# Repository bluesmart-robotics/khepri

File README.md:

# KHÉPRI — Blue Smart Robotics

- [`IHM/`](IHM/) : écrans pilote — rond 1,75" (régime moteur) et rectangulaire 1,64" (énergie),
  sur cartes Waveshare ESP32-S3-Touch-AMOLED — documentation et code, mises à jour OTA depuis ce dépôt.
- [`hardware/BSR flight power module/`](hardware/BSR%20flight%20power%20module/) : instrument de vol
  de 80 mm — commande moteur BSR Drive v3.7 (sous-module), carte de contrôle CAN et interface pilote.
  Contient un sous-module : cloner avec `--recurse-submodules`.
  - [`ecran_rond_1.75/`](hardware/BSR%20flight%20power%20module/ecran_rond_1.75/) : carte écran rond
    1,75" propre à KHEPRI (KiCad 9), dérivée de la Waveshare sans PMU/batterie, micros ni IMU —
    schéma complet, PCB Ø46 mm à router.

L'ancien code de démonstration de l'écran AMOLED 1,64" (bsr_screen) reste consultable dans
l'historique Git (commit 8a9e916).

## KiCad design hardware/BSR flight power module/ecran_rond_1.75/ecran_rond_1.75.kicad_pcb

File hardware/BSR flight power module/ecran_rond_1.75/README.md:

# Écran rond 1,75" KHEPRI — carte dérivée de la Waveshare ESP32-S3-Touch-AMOLED-1.75-G

Reproduction en KiCad 9 de la carte Waveshare **ESP32-S3-Touch-AMOLED-1.75(-G)** (écran AMOLED rond
466×466 sur ESP32-S3R8), adaptée à l'instrument de bord KHEPRI :

- **supprimé** : gestion de batterie (AXP2101, connecteur batterie, bouton PWR), micros et leur ADC
  (ES7210, 2 micros MEMS, circuit d'annulation d'écho), centrale inertielle (QMI8658) ;
- **ajouté / modifié** : entrée 5 V sur connecteur JST PH 4 points (+5 V, GND, TX, RX) partagé avec
  l'UART vers la carte façade, buck AP63203 3,3 V 2 A (même famille que l'AP63205 de la carte de
  contrôle), pile CR1220 (support CMS, côté écran) pour la RTC et le GPS externe ;
- **GPS déporté** : le module LC76G et son antenne sont retirés de la carte (place nécessaire au module
  ESP32) et remplacés par un connecteur **JST SH 6 points (J7)** pour un module GPS externe en I2C ;
- **MCU remplacé par un module certifié** : ESP32-S3-WROOM-1-N16R8 (même puce ESP32-S3R8, 16 Mo de
  flash, 8 Mo de PSRAM octale, antenne PCB intégrée, certifications radio CE/FCC/IC du module) à la
  place de la puce nue + flash + quartz + antenne céramique de la Waveshare ;
- **conservé à l'identique** : brochage ESP32 (mêmes GPIO), nappe écran 31 points (CO5300 QSPI + tactile
  CST9217 I2C), codec ES8311 + ampli NS4150B + haut-parleur, RTC PCF85063, extenseur TCA9554,
  microSD en SDMMC 1 bit, USB-C natif, boutons BOOT et RESET.

Le brochage ESP32 est **le même** que celui de la carte Waveshare (voir
[`../../../IHM/documentation/ecran_rond_1.75/SYNTHESE_carte_1.75.md`](../../../IHM/documentation/ecran_rond_1.75/SYNTHESE_carte_1.75.md)),
donc le code de [`IHM/code/ecran_rond_1.75`](../../../IHM/code/ecran_rond_1.75) tourne dessus avec
trois adaptations (voir § Firmware).

État : **v0.2 — schéma complet (ERC = 0), netlist vérifiée, PCB Ø46 mm 4 couches avec empreintes,
nets, netclasses et placement optimisé sur les deux faces (DRC sans erreur). Routage à faire.**

## Contenu

| Fichier | Rôle |
|---|---|
| `ecran_rond_1.75.kicad_pro` / `.kicad_sch` | Projet KiCad 9.0 ; feuille racine + 5 sous-feuilles |
| `alimentation.kicad_sch` | USB-C, JST 5 V, OU à diodes, buck 3,3 V, 3,3 V analogique, pile RTC |
| `mcu.kicad_sch` | Module ESP32-S3-WROOM-1-N16R8, découplage, USB, BOOT/RESET, points de test |
| `ecran.kicad_sch` | Nappe FH26-31S (CO5300 + CST9217), découplage, pull-ups I2C |
| `audio.kicad_sch` | ES8311, NS4150B, connecteur haut-parleur MX1.25 |
| `peripheriques.kicad_sch` | TCA9554, PCF85063 + 32,768 kHz, microSD, connecteur GPS externe J7, trous M2 |
| `ecran_rond_1.75.kicad_pcb` | PCB Ø46 mm, 4 couches (F.Cu / In1 GND / In2 GND / B.Cu), 1,0 mm, ENIG |
| `lib/` | Symboles propres (ES8311, NS4150B ; LC76G conservé mais inutilisé) et `ecran_rond.3dshapes/` : modèles STEP simplifiés aux cotes constructeur pour les boîtiers absents de la bibliothèque KiCad (USB-C HRO TYPE-C-31-M-12, inductance NR4018, QFN-20 3×3 de l'ES8311, DFN-10 2,6×2,6 du PCF85063), générés par `generateur/models3d.py` |
| `bom.csv` | Nomenclature (`;` comme séparateur) |
| `netlist.txt`, `placement.csv` | Netlist de référence (vérifiée identique à celle exportée par KiCad) et placement des empreintes |
| `doc/schema.pdf`, `doc/placement_v0.2.png` | Schéma imprimé, aperçu du placement (faces F et B) |
| `generateur/` | Scripts Python qui ont produit schéma et PCB (voir plus bas) |

Le schéma est **généré** : chaque composant est posé sur une grille et chaque broche porte une étiquette
globale (ou un symbole d'alimentation). C'est lisible mais pas « dessiné » ; on peut réarranger à la
main dans KiCad sans rien casser, les connexions sont dans les étiquettes.

## Architecture d'alimentation

```
USB-C (VBUS) ─B5819W─┐
                     ├─ +5V ── AP63203 (4,7 µH, 2×22 µF) ── +3V3 ── ESP32, écran, SD, GPS ext. (J7), TCA9554, ES8311 (num.), NS4150B
JST J2 (+5V_IN) B5819W                                       ├─ perle ferrite ── A3V3 (ES8311 analogique)
                                                             └─ BAT54C ─┬─ VCC_RTC ── PCF85063
                                                   CR1220 ── BAT54C ────┘
```

- Les deux sources 5 V sont découplées par diodes Schottky (B5819W, SOD-123, 1 A) : on peut laisser l'USB branché
  pour flasher pendant que l'instrument alimente la carte.
- Pas de PMU : plus de bouton PWR ni d'extinction logicielle ; la carte démarre dès que le 5 V est là.
- `AGND` (audio) est relié à `GND` par un net-tie (NT1) : un seul point de masse.
- L'écran AMOLED n'a pas de rétroéclairage : la luminosité se règle par commandes CO5300 (comme sur
  la Waveshare), toute l'alimentation du panneau est en 3,3 V sur la nappe.

## Connecteurs

| Rep. | Type | Brochage |
|---|---|---|
| J1 | USB-C 16P (HRO TYPE-C-31-M-12) | USB 2.0 natif ESP32-S3 (GPIO19/20), flash + logs ; CC 5,1 kΩ ; ESD USBLC6-2SC6 ; TVS SMF5.0A |
| J2 | JST PH 2,0 mm 4 points | 1 = +5 V entrée · 2 = GND · 3 = **TX** (GPIO17, sortie ESP32) · 4 = **RX** (GPIO18) — vers la carte façade |
| J3 | Hirose FH26-31S-0.3SHW | Nappe de l'écran, brochage relevé sur le schéma Waveshare (pins 2-3, 5-6, 8-9, 19, 24 NC ; 21-23 et 26 = 3,3 V) |
| J5 | Molex PicoBlade 1,25 mm 2P (= MX1.25) | Haut-parleur 8 Ω 2 W |
| J6 | microSD Hirose DM3AT | SDMMC 1 bit (CMD GPIO1, CLK GPIO2, D0 GPIO3, D3/CS GPIO41) |
| J7 | JST SH 1,0 mm 6 points (SM06B-SRSS-TB), face F, au bord | GPS externe : 1 = +3V3 · 2 = GND · 3 = SDA · 4 = SCL · 5 = GPS_RST (TCA9554 P7) · 6 = 1PPS (GPIO21) |
| BT1 | Support CMS CR1220 (Linx BAT-HLD-012-SMT), côté écran | Sauvegarde de la RTC PCF85063 (plusieurs années, ≈ 0,25 µA) |
| H1–H3 | Trous M2 | Positions provisoires, à caler sur la mécanique de l'instrument |

## Brochage ESP32-S3 (inchangé par rapport à Waveshare)

| GPIO | Signal | GPIO | Signal |
|---:|---|---:|---|
| 0 | BOOT (bouton, pull-up) | 19 / 20 | USB D− / D+ (22 Ω en série) |
| 1 / 2 / 3 | SD_CMD / SD_CLK / SD_D0 | 21 | 1PPS du GPS externe (J7 broche 6) |
| 4–7 | QSPI SIO0–SIO3 écran | 38 | QSPI_SCL écran |
| 8 | I2S DSDIN → ES8311 | 39 / 40 | LCD_RESET / TP_RESET |
| 9 | I2S SCLK | 41 | SDCS (microSD D3) |
| 10 | I2S ASDOUT ← ES8311 (libre côté codec, sans micro) | 42 | I2S MCLK |
| 11 | TP_INT tactile | 43 / 44 | UART0 TX / RX (console, points de test TP3/TP4) |
| 12 / 13 | LCD_CS / LCD_TE | 45 | I2S LRCK |
| 14 / 15 | I2C SCL / SDA (2,2 kΩ) | 46 | PA_CTRL (ampli, pull-down 10 kΩ) |
| 16 | libre (point de test TP1) | 35–37 | **réservés** PSRAM octale du module, non sortis |
| 17 / 18 | **UART façade TX / RX** (J2) | | |

Bus I2C (0x5A tactile, 0x18 ES8311, 0x20 TCA9554, 0x51 PCF85063, + le GPS externe sur J7 — 0x50/0x54 pour un LC76G comme sur la Waveshare).
TCA9554 : P3 = RTC_INT (pull-up 10 kΩ), P7 = GPS_RST ; P0–P2 et P4–P6 non utilisés.

## PCB

- Contour : cercle Ø46 mm comme la Waveshare (pas encore les encoches latérales pour les boutons ;
  à reprendre avec le dessin coté `IHM/documentation/ecran_rond_1.75/3D/`). Épaisseur 1,0 mm.
- Faces : l'écran est collé sur la face **B.Cu** ; n'y vont que des composants plats (≤ 2,5 mm) :
  nappe J3, microSD J6, pile BT1, codec U4, ampli U5 et leurs passifs. Le module ESP32-S3-WROOM-1
  (3,1 mm), l'USB-C, le JST façade, le GPS J7, le buck, la RTC, l'extenseur et les boutons sont
  sur la face **F.Cu**, à l'arrière de l'instrument.
- Module : antenne PCB tournée vers le bord gauche, débordant légèrement du cercle comme le
  recommande Espressif (antenne au ras ou hors de la carte). Zone `keepout_antenne_WROOM` sur les
  4 couches (ni piste, ni via, ni plan) = courtyard Espressif, 15 mm de chaque côté de l'antenne.
  Rien côté B sous les vias thermiques du pad central (GND) du module.
- microSD : fente vers le bord (bas de la carte), contacts vers le centre.
- Zones GND sur In1, In2, B.Cu et F.Cu (remplies).
- Placement (voir `doc/placement_v0.2.png`) : gros composants placés par recuit simulé
  (`generateur/placer.py` : pas de chevauchement, connecteurs au bord, fente microSD vers
  l'extérieur, antenne au bord, trous M2 écartés, longueur de fil minimisée), passifs près de leur
  circuit par recherche gloutonne. **DRC : 3 erreurs « starved thermal »** (pads GND de J1 et U7 qui
  n'ont qu'un rayon de frein thermique vers le plan F avant routage — disparaissent au routage),
  reste des avertissements de sérigraphie à nettoyer après routage.
- **Routage à faire** (freerouting ou à la main). Netclasses déjà définies dans le projet :
  `USB_90R` (paire USB_N/USB_P 0,18 / 0,18 mm — à recalculer avec le calculateur d'impédance du
  stackup retenu), `Alim` (0,5 mm, vias 0,8/0,4), `QSPI_ecran` (0,15 mm, QSPI_* et LCD_*),
  `Default` 0,2 mm, isolation 0,15 mm. Règles mini : 0,127 mm piste/isolation, via 0,45/0,2 mm,
  trou 0,2 mm (JLCPCB 4 couches). Contraintes : QSPI écran court et groupé (U1 → J3), rien dans la
  zone d'antenne, boucle du buck (U2, L1, C4/C5) compacte, plans GND In1/In2 continus sous l'USB.

## Firmware (`IHM/code/ecran_rond_1.75`)

Le code gère les deux cartes : `idf.py menuconfig` → « KHEPRI - ecran rond 1.75 » → *Carte* =
**Carte ecran rond KHEPRI (BSR)**. Ce choix :

1. remplace le bouton PWR (AXP2101 / TCA9554 P4) par le bouton **BOOT** (GPIO0) dans `kh_pwr_pressed()` ;
2. désactive les gestes à l'accéléromètre (pas de QMI8658) — la consigne viendra du bouton haptique ;
3. initialise l'**UART1 façade** sur GPIO17 (TX) / GPIO18 (RX), 115200 bauds (`kh_facade_uart_*`).
   Transport seulement : le protocole IHM (aujourd'hui en ESP-NOW, `khepri_link`) reste à porter
   dessus. Le GPS (externe, sur J7) reste en I2C ; son 1PPS arrive sur GPIO21.

## Regénérer les fichiers

`generateur/design.py` décrit toute la carte (composants, valeurs, empreintes, nets) ; `gen.py`
produit les feuilles de schéma, la bibliothèque projet, le `.kicad_pro`, la BOM et la netlist ;
`pcbgen.py` produit le `.kicad_pcb` (contour, nets, placement). Ils lisent les bibliothèques KiCad 9
officielles (`symbols/` et `footprints/`) dont le chemin est en tête de `symlib.py` / `fplib.py`.
`placer.py` optimise la position des gros composants (sortie `placement_big.json`, lue par
`pcbgen.py`). Après génération, les composants de la face B sont retournés dans KiCad (le script
les écrit tous côté F) : liste dans `placement.csv`, colonne `face`.
Attention à la convention de rotation au retournement : pour une empreinte de `placement.csv` en face B
avec la rotation *r*, la rotation finale dans KiCad (après retournement) doit valoir *r* ; avec
`batch_move_components` (MCP KiCad) cela revient à demander `rotation = 180 − r` avec `layer = B.Cu`.
`placer.py design_export.json SEED ITER [init.json REF1,REF2,…]` : la forme longue raffine un placement
existant en ne bougeant que les références listées ; `run_sa.sh` lance les recuits deux par deux.

Sources : schéma Waveshare (`IHM/documentation/ecran_rond_1.75/schema/`), `HARDWARE_REFERENCE.md` et
BSP ESP-IDF du dépôt officiel `waveshareteam/ESP32-S3-Touch-AMOLED-1.75`.

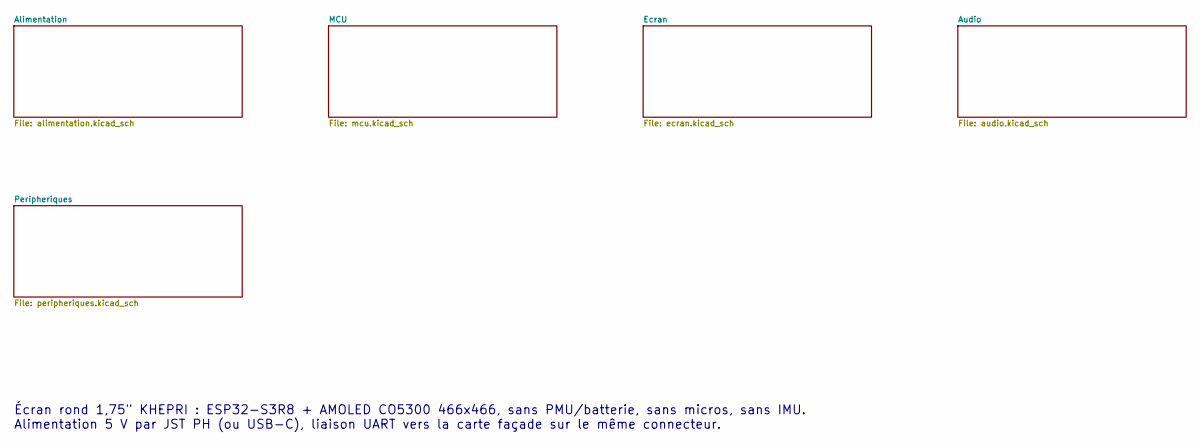
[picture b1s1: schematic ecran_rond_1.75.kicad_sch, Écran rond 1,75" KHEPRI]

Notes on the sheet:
Écran rond 1,75" KHEPRI : ESP32-S3R8 + AMOLED CO5300 466x466, sans PMU/batterie, sans micros, sans IMU. Alimentation 5 V par JST PH (ou USB-C), liaison UART vers la carte façade sur le même connecteur.

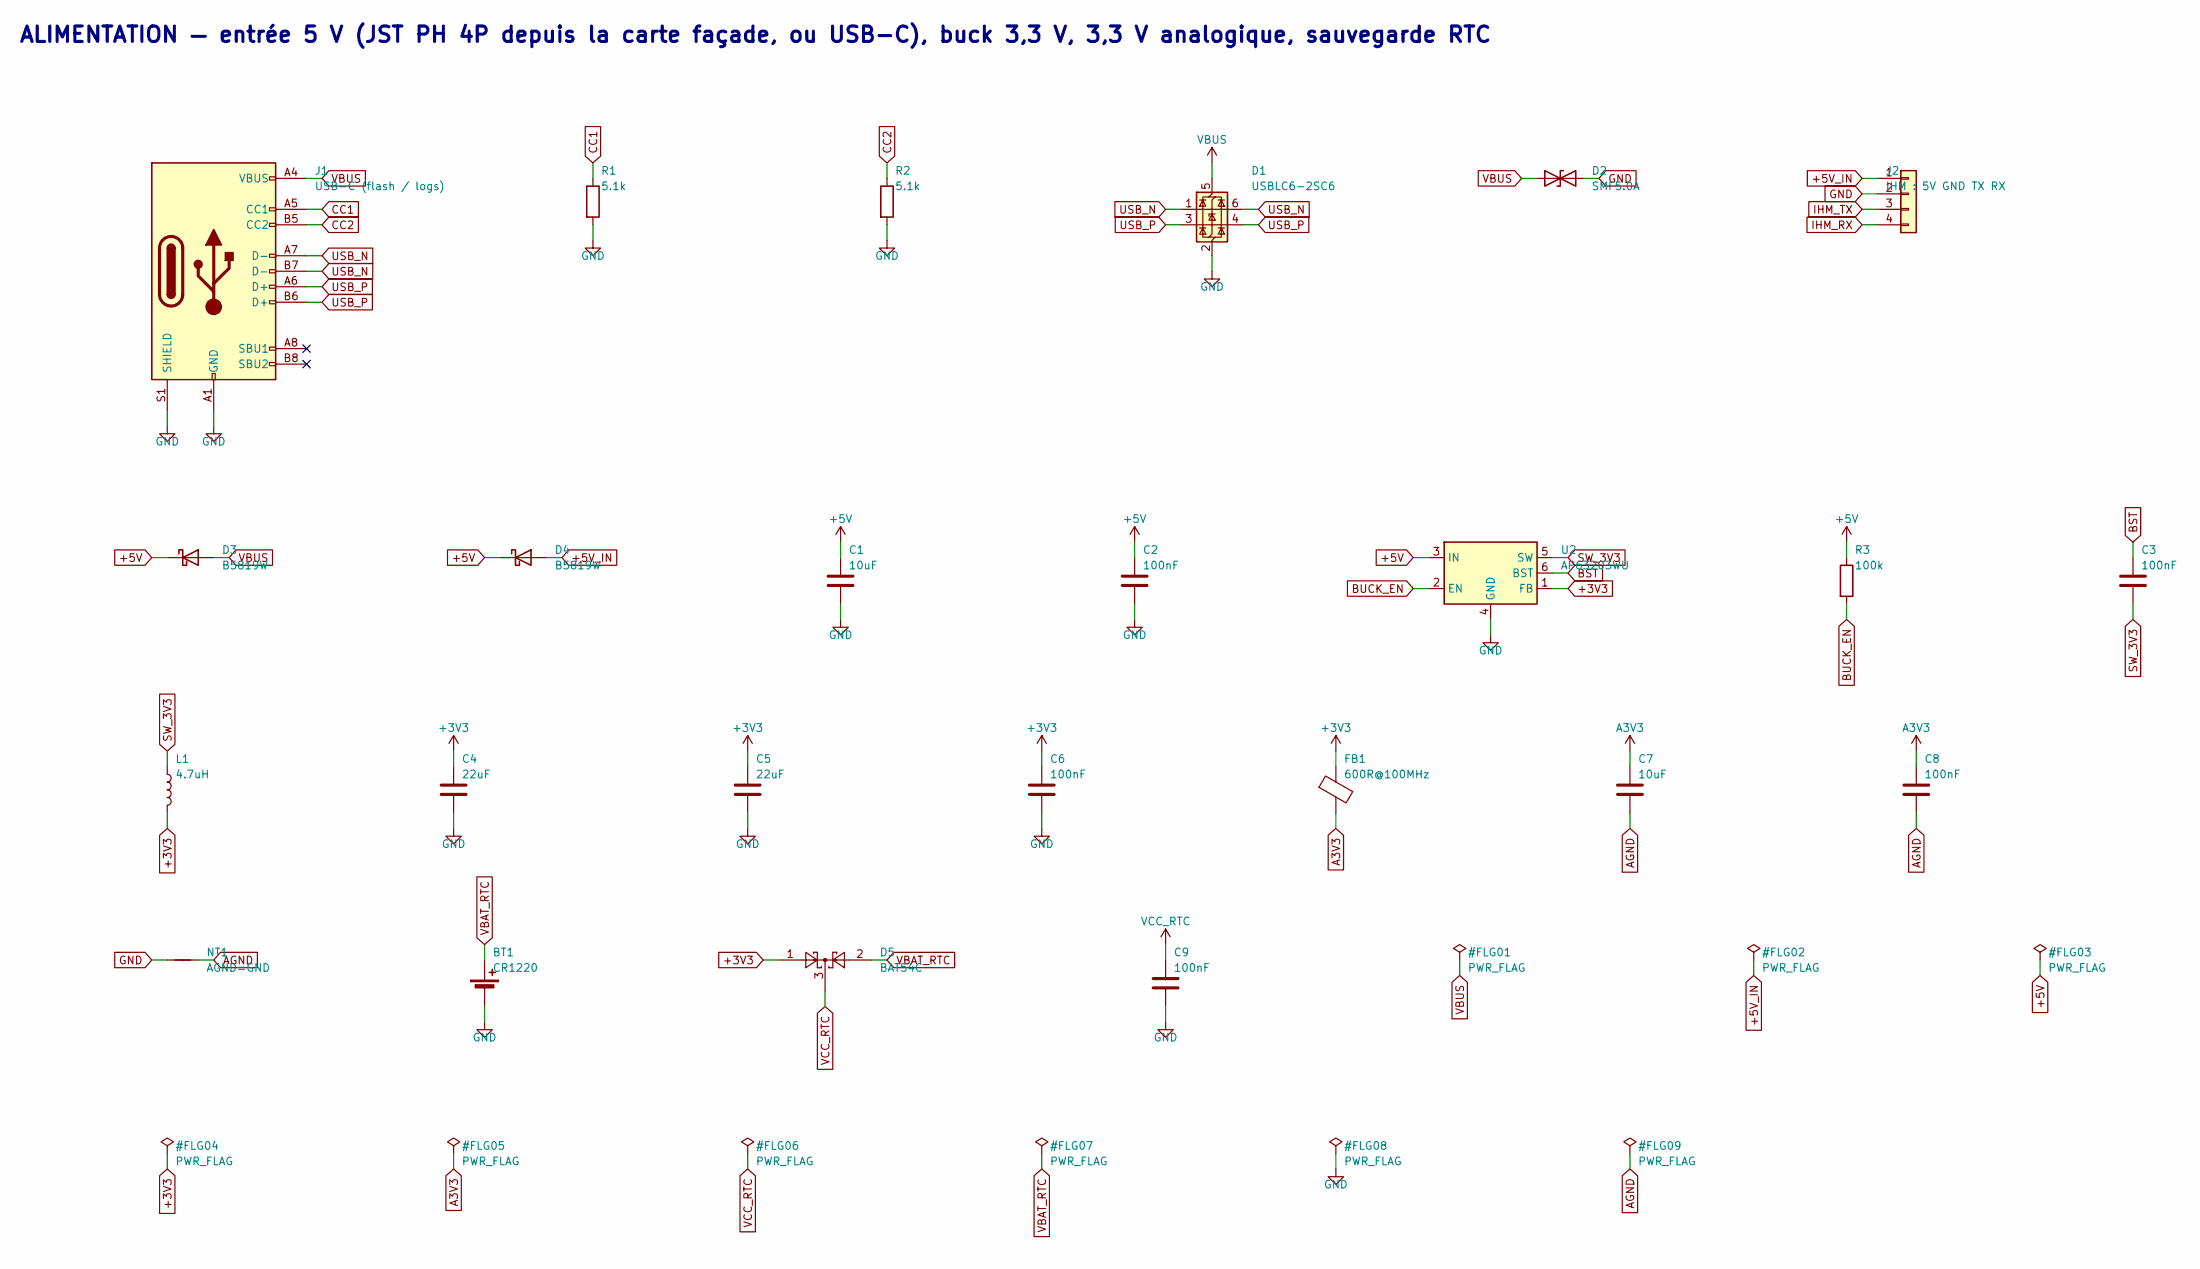
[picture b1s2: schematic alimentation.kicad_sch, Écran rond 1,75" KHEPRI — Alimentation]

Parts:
BT1: CR1220; BatteryHolder_LINX_BAT-HLD-012-SMT
C1, C7: 10uF; C_0805_2012Metric
C2, C3, C6, C8, C9: 100nF; C_0402_1005Metric
C4, C5: 22uF; C_0805_2012Metric
D1: USBLC6-2SC6; SOT-23-6
D2: SMF5.0A; D_SOD-123F
D3, D4: B5819W; D_SOD-123
D5: BAT54C; SOT-23
FB1: 600R@100MHz; L_0603_1608Metric
J1: USB-C (flash / logs); USB_C_Receptacle_HRO_TYPE-C-31-M-12
J2: IHM : 5V GND TX RX; JST_PH_B4B-PH-K_1x04_P2.00mm_Vertical
L1: 4.7uH; L_Taiyo-Yuden_NR-40xx
NT1: AGND=GND; NetTie-2_SMD_Pad0.5mm
R1, R2: 5.1k; R_0402_1005Metric
R3: 100k; R_0402_1005Metric
U2: AP63203WU; TSOT-23-6

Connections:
+3V3: C4.1, C5.1, C6.1, D5.1, FB1.1, L1.2, U2.1 (FB); also elsewhere on the board
+5V: C1.1, C2.1, D3.1 (K), D4.1 (K), R3.1, U2.3 (IN)
+5V_IN: D4.2 (A), J2.1
A3V3: C7.1, C8.1, FB1.2; also elsewhere on the board
AGND: C7.2, C8.2, NT1.2; also elsewhere on the board
BST: C3.1, U2.6 (BST)
BUCK_EN: R3.2, U2.2 (EN)
CC1: J1.A5 (CC1), R1.1
CC2: J1.B5 (CC2), R2.1
GND: BT1.2 (-), C1.2, C2.2, C4.2, C5.2, C6.2, C9.2, D1.2 (GND), D2.2 (A2), J1.A1 (GND), J1.A12 (GND), J1.B1 (GND), J1.B12 (GND), J1.S1 (SHIELD), J2.2, NT1.1, R1.2, R2.2, U2.4 (GND); also elsewhere on the board
IHM_RX: J2.4; also elsewhere on the board
IHM_TX: J2.3; also elsewhere on the board
SW_3V3: C3.2, L1.1, U2.5 (SW)
USB_N: D1.1 (I/O1), D1.6 (I/O1), J1.A7 (D-), J1.B7 (D-); also elsewhere on the board
USB_P: D1.3 (I/O2), D1.4 (I/O2), J1.A6 (D+), J1.B6 (D+); also elsewhere on the board
VBAT_RTC: BT1.1 (+), D5.2
VBUS: D1.5 (VBUS), D2.1 (A1), D3.2 (A), J1.A4 (VBUS), J1.A9 (VBUS), J1.B4 (VBUS), J1.B9 (VBUS)
VCC_RTC: C9.1, D5.3; also elsewhere on the board

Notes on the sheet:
ALIMENTATION — entrée 5 V (JST PH 4P depuis la carte façade, ou USB-C), buck 3,3 V, 3,3 V analogique, sauvegarde RTC

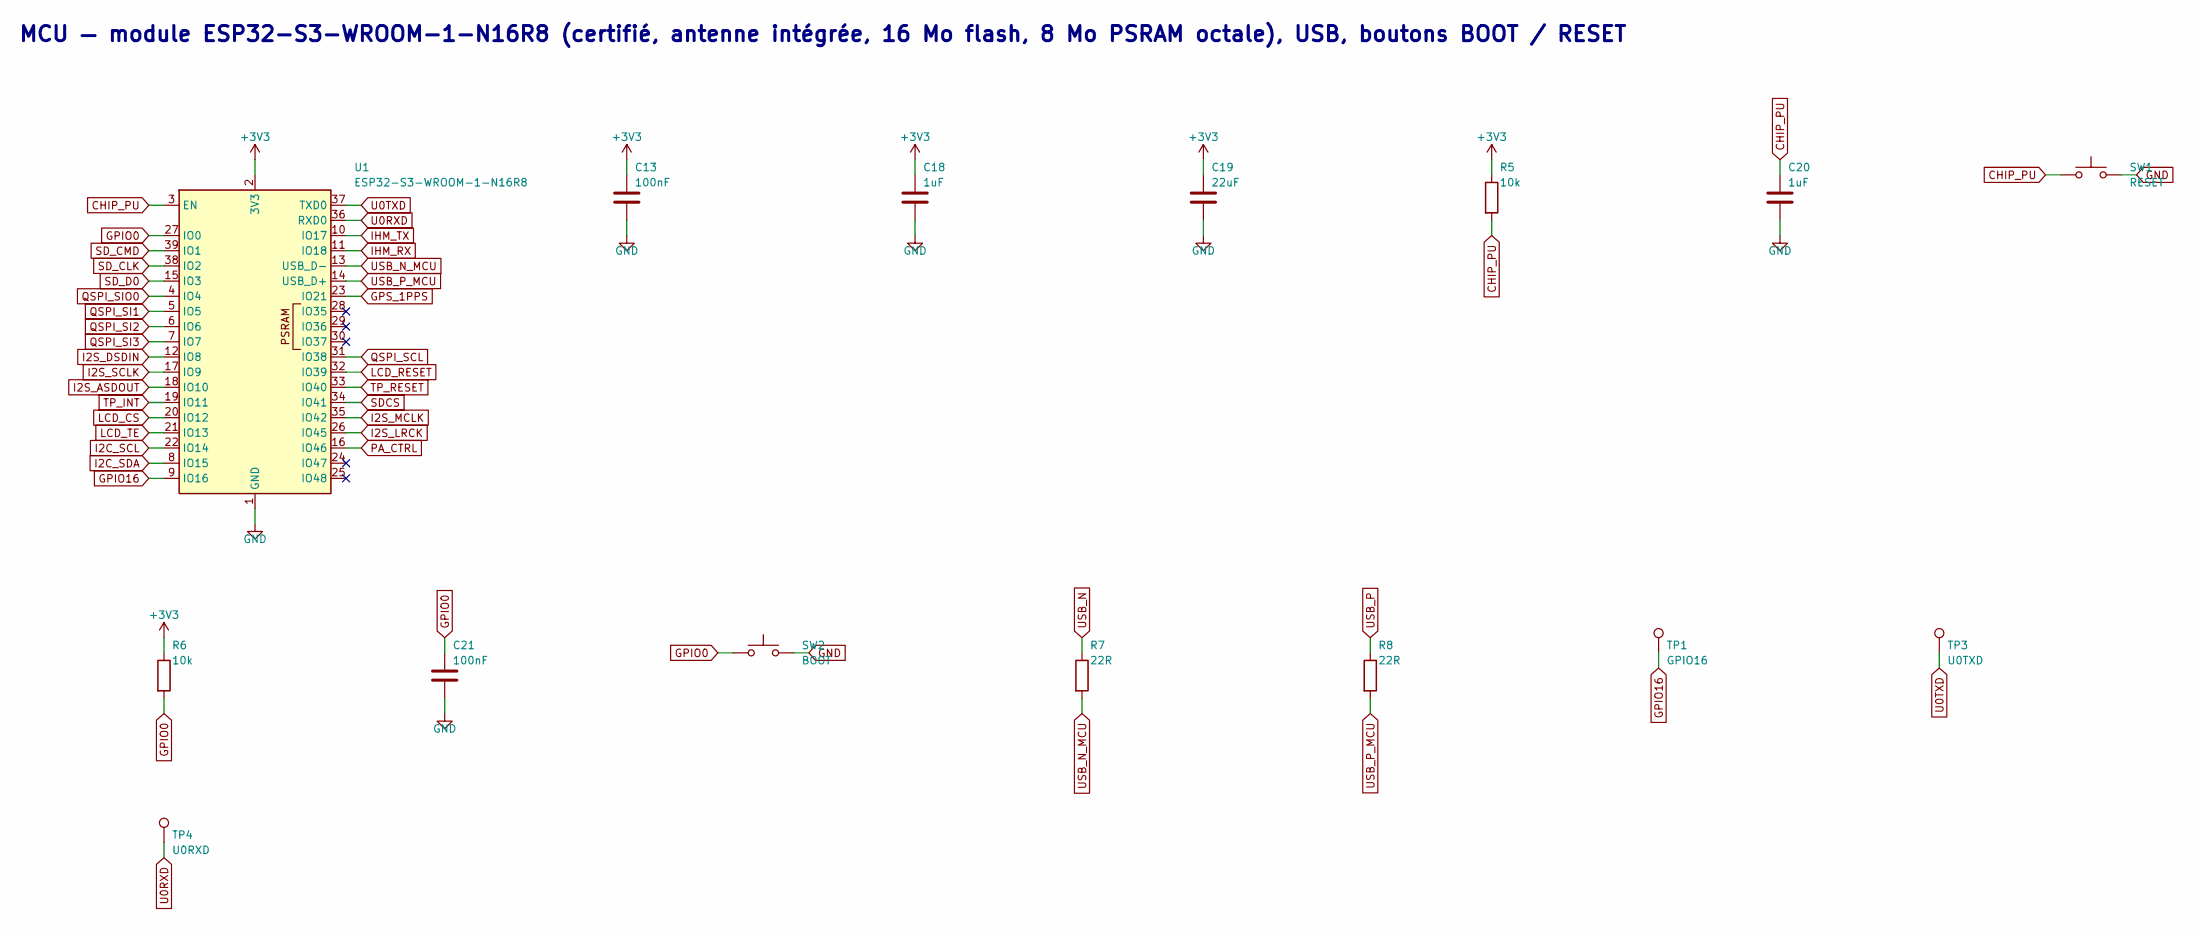
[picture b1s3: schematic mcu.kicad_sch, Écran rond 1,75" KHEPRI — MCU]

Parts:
C13, C21: 100nF; C_0402_1005Metric
C18, C20: 1uF; C_0402_1005Metric
C19: 22uF; C_0805_2012Metric
R5, R6: 10k; R_0402_1005Metric
R7, R8: 22R; R_0402_1005Metric
SW1: RESET; SW_SPST_PTS810
SW2: BOOT; SW_SPST_PTS810
TP1: GPIO16; TestPoint_Pad_D1.0mm
TP3: U0TXD; TestPoint_Pad_D1.0mm
TP4: U0RXD; TestPoint_Pad_D1.0mm
U1: ESP32-S3-WROOM-1-N16R8; ESP32-S3-WROOM-1

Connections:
+3V3: C13.1, C18.1, C19.1, R5.1, R6.1, U1.2 (3V3); also elsewhere on the board
CHIP_PU: C20.1, R5.2, SW1.1, U1.3 (EN)
GND: C13.2, C18.2, C19.2, C20.2, C21.2, SW1.2, SW2.2, U1.1 (GND), U1.40 (GND), U1.41 (GND); also elsewhere on the board
GPIO0: C21.1, R6.2, SW2.1, U1.27 (IO0)
GPIO16: TP1.1, U1.9 (IO16)
GPS_1PPS: U1.23 (IO21); also elsewhere on the board
I2C_SCL: U1.22 (IO14); also elsewhere on the board
I2C_SDA: U1.8 (IO15); also elsewhere on the board
I2S_ASDOUT: U1.18 (IO10); also elsewhere on the board
I2S_DSDIN: U1.12 (IO8); also elsewhere on the board
I2S_LRCK: U1.26 (IO45); also elsewhere on the board
I2S_MCLK: U1.35 (IO42); also elsewhere on the board
I2S_SCLK: U1.17 (IO9); also elsewhere on the board
IHM_RX: U1.11 (IO18); also elsewhere on the board
IHM_TX: U1.10 (IO17); also elsewhere on the board
LCD_CS: U1.20 (IO12); also elsewhere on the board
LCD_RESET: U1.32 (IO39); also elsewhere on the board
LCD_TE: U1.21 (IO13); also elsewhere on the board
PA_CTRL: U1.16 (IO46); also elsewhere on the board
QSPI_SCL: U1.31 (IO38); also elsewhere on the board
QSPI_SI1: U1.5 (IO5); also elsewhere on the board
QSPI_SI2: U1.6 (IO6); also elsewhere on the board
QSPI_SI3: U1.7 (IO7); also elsewhere on the board
QSPI_SIO0: U1.4 (IO4); also elsewhere on the board
SDCS: U1.34 (IO41); also elsewhere on the board
SD_CLK: U1.38 (IO2); also elsewhere on the board
SD_CMD: U1.39 (IO1); also elsewhere on the board
SD_D0: U1.15 (IO3); also elsewhere on the board
TP_INT: U1.19 (IO11); also elsewhere on the board
TP_RESET: U1.33 (IO40); also elsewhere on the board
U0RXD: TP4.1, U1.36 (RXD0)
U0TXD: TP3.1, U1.37 (TXD0)
USB_N: R7.1; also elsewhere on the board
USB_N_MCU: R7.2, U1.13 (USB_D-)
USB_P: R8.1; also elsewhere on the board
USB_P_MCU: R8.2, U1.14 (USB_D+)

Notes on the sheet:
MCU — module ESP32-S3-WROOM-1-N16R8 (certifié, antenne intégrée, 16 Mo flash, 8 Mo PSRAM octale), USB, boutons BOOT / RESET

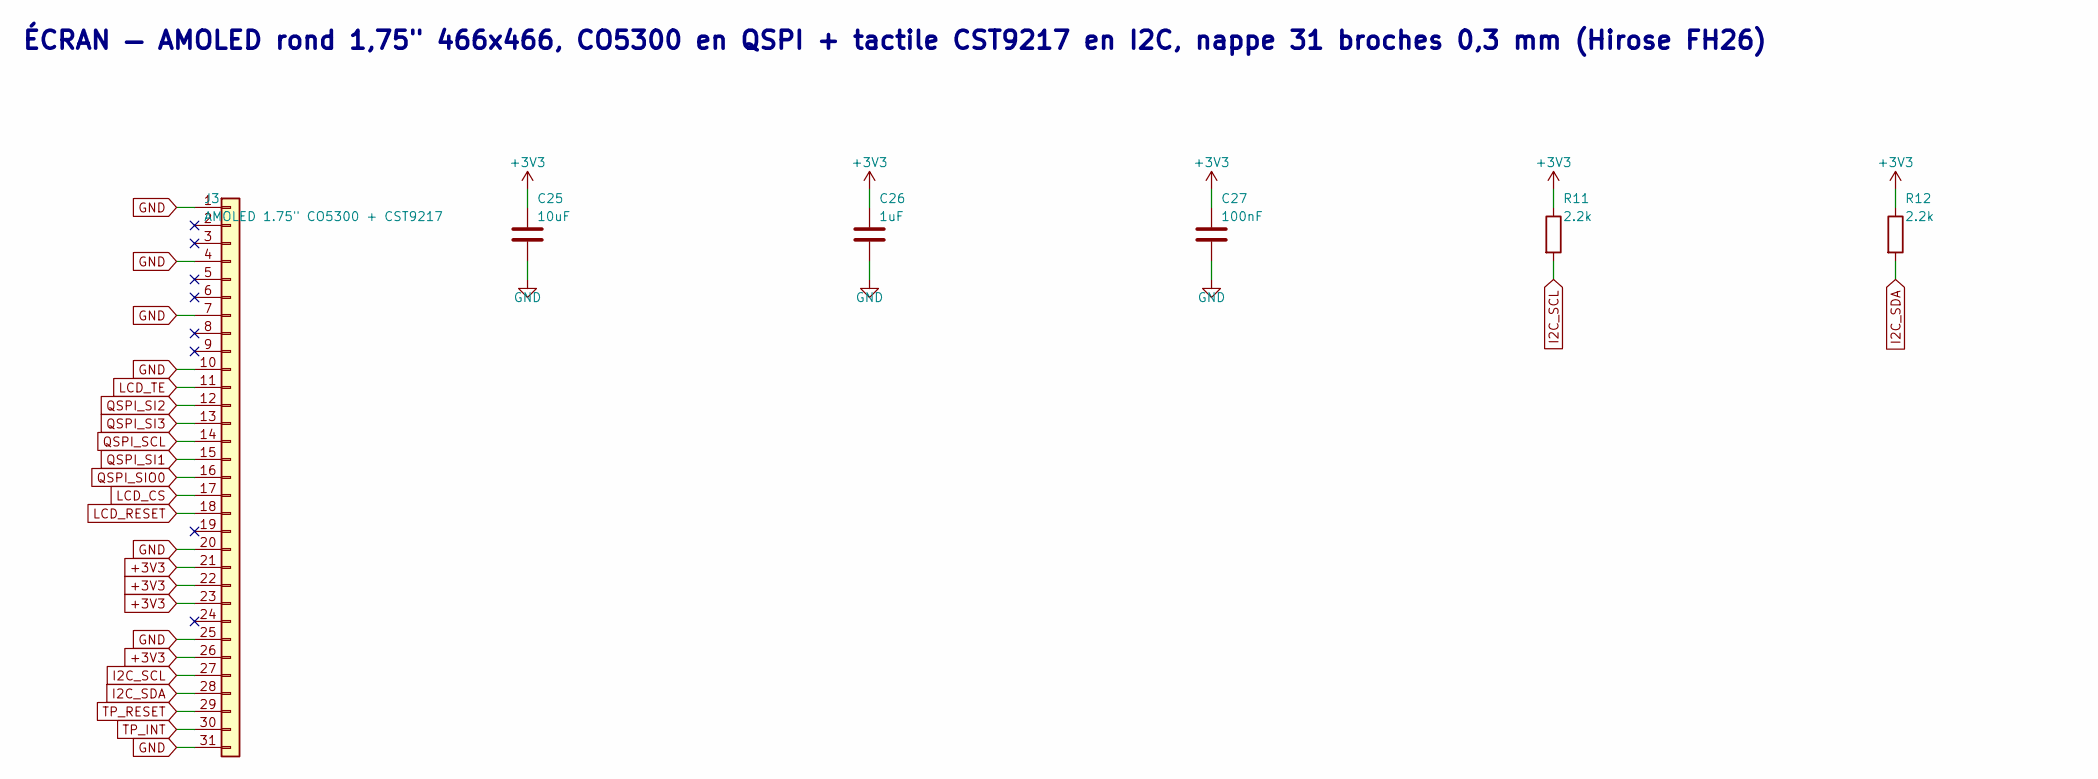
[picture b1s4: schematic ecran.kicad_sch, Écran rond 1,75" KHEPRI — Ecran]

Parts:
C25: 10uF; C_0805_2012Metric
C26: 1uF; C_0402_1005Metric
C27: 100nF; C_0402_1005Metric
J3: AMOLED 1.75" CO5300 + CST9217; Hirose_FH26-31S-0.3SHW_2Rows-31Pins-1MP_P0.60mm_Horizontal
R11, R12: 2.2k; R_0402_1005Metric

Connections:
+3V3: C25.1, C26.1, C27.1, J3.21, J3.22, J3.23, J3.26, R11.1, R12.1; also elsewhere on the board
GND: C25.2, C26.2, C27.2, J3.1, J3.4, J3.7, J3.10, J3.20, J3.25, J3.31; also elsewhere on the board
I2C_SCL: J3.27, R11.2; also elsewhere on the board
I2C_SDA: J3.28, R12.2; also elsewhere on the board
LCD_CS: J3.17; also elsewhere on the board
LCD_RESET: J3.18; also elsewhere on the board
LCD_TE: J3.11; also elsewhere on the board
QSPI_SCL: J3.14; also elsewhere on the board
QSPI_SI1: J3.15; also elsewhere on the board
QSPI_SI2: J3.12; also elsewhere on the board
QSPI_SI3: J3.13; also elsewhere on the board
QSPI_SIO0: J3.16; also elsewhere on the board
TP_INT: J3.30; also elsewhere on the board
TP_RESET: J3.29; also elsewhere on the board

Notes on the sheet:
ÉCRAN — AMOLED rond 1,75" 466x466, CO5300 en QSPI + tactile CST9217 en I2C, nappe 31 broches 0,3 mm (Hirose FH26)

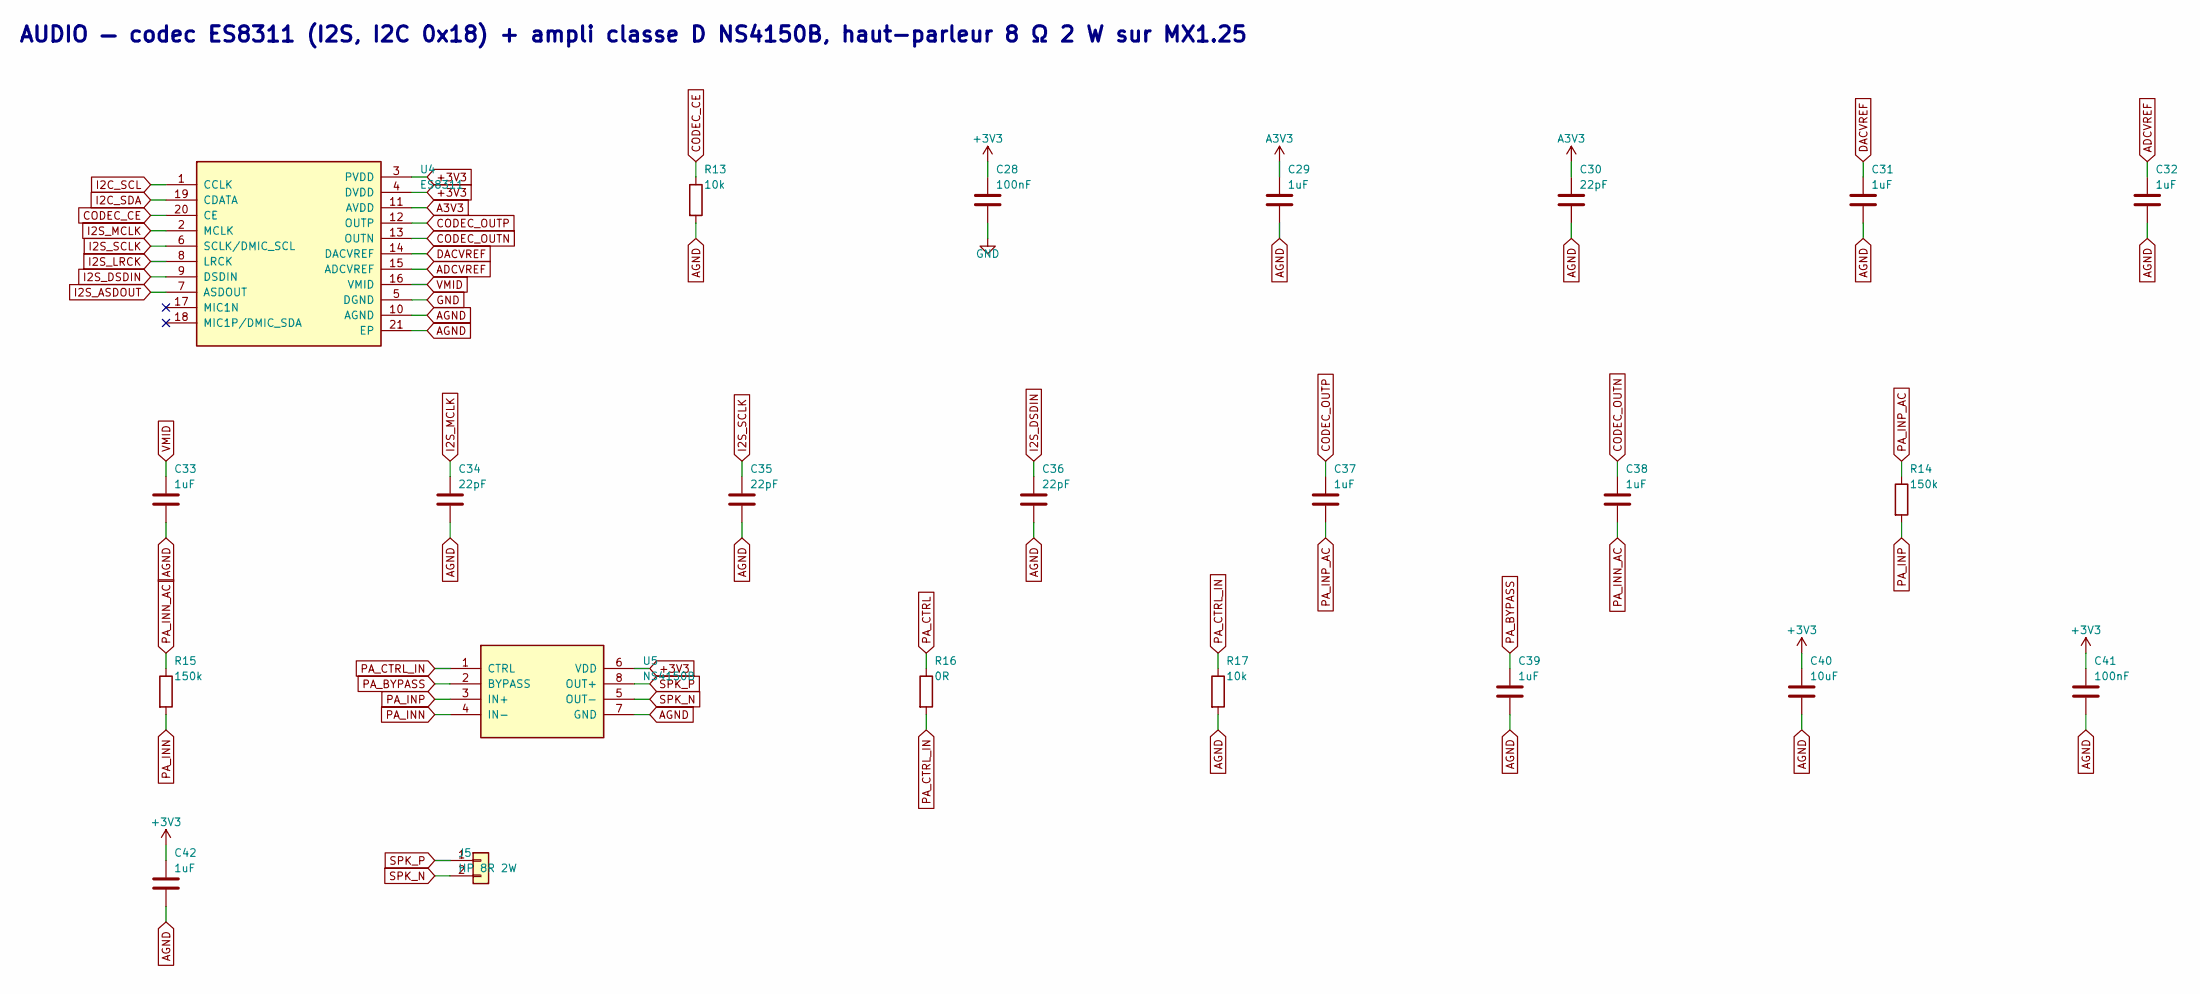
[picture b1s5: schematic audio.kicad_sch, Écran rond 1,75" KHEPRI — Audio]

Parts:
C28, C41: 100nF; C_0402_1005Metric
C29, C31, C32, C33, C39, C42: 1uF; C_0402_1005Metric
C30, C34, C35, C36: 22pF; C_0402_1005Metric
C37, C38: 1uF; C_0603_1608Metric
C40: 10uF; C_0805_2012Metric
J5: HP 8R 2W; Molex_PicoBlade_53398-0271_1x02-1MP_P1.25mm_Vertical
R13, R17: 10k; R_0402_1005Metric
R14, R15: 150k; R_0402_1005Metric
R16: 0R; R_0402_1005Metric
U4: ES8311; QFN-20-1EP_3x3mm_P0.4mm_EP1.65x1.65mm
U5: NS4150B; SOIC-8_3.9x4.9mm_P1.27mm

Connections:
+3V3: C28.1, C40.1, C41.1, C42.1, U4.3 (PVDD), U4.4 (DVDD), U5.6 (VDD); also elsewhere on the board
A3V3: C29.1, C30.1, U4.11 (AVDD); also elsewhere on the board
ADCVREF: C32.1, U4.15 (ADCVREF)
AGND: C29.2, C30.2, C31.2, C32.2, C33.2, C34.2, C35.2, C36.2, C39.2, C40.2, C41.2, C42.2, R13.2, R17.2, U4.10 (AGND), U4.21 (EP), U5.7 (GND); also elsewhere on the board
CODEC_CE: R13.1, U4.20 (CE)
CODEC_OUTN: C38.1, U4.13 (OUTN)
CODEC_OUTP: C37.1, U4.12 (OUTP)
DACVREF: C31.1, U4.14 (DACVREF)
GND: C28.2, U4.5 (DGND); also elsewhere on the board
I2C_SCL: U4.1 (CCLK); also elsewhere on the board
I2C_SDA: U4.19 (CDATA); also elsewhere on the board
I2S_ASDOUT: U4.7 (ASDOUT); also elsewhere on the board
I2S_DSDIN: C36.1, U4.9 (DSDIN); also elsewhere on the board
I2S_LRCK: U4.8 (LRCK); also elsewhere on the board
I2S_MCLK: C34.1, U4.2 (MCLK); also elsewhere on the board
I2S_SCLK: C35.1, U4.6 (SCLK/DMIC_SCL); also elsewhere on the board
PA_BYPASS: C39.1, U5.2 (BYPASS)
PA_CTRL: R16.1; also elsewhere on the board
PA_CTRL_IN: R16.2, R17.1, U5.1 (CTRL)
PA_INN: R15.2, U5.4 (IN-)
PA_INN_AC: C38.2, R15.1
PA_INP: R14.2, U5.3 (IN+)
PA_INP_AC: C37.2, R14.1
SPK_N: J5.2, U5.5 (OUT-)
SPK_P: J5.1, U5.8 (OUT+)
VMID: C33.1, U4.16 (VMID)

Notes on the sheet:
AUDIO — codec ES8311 (I2S, I2C 0x18) + ampli classe D NS4150B, haut-parleur 8 Ω 2 W sur MX1.25

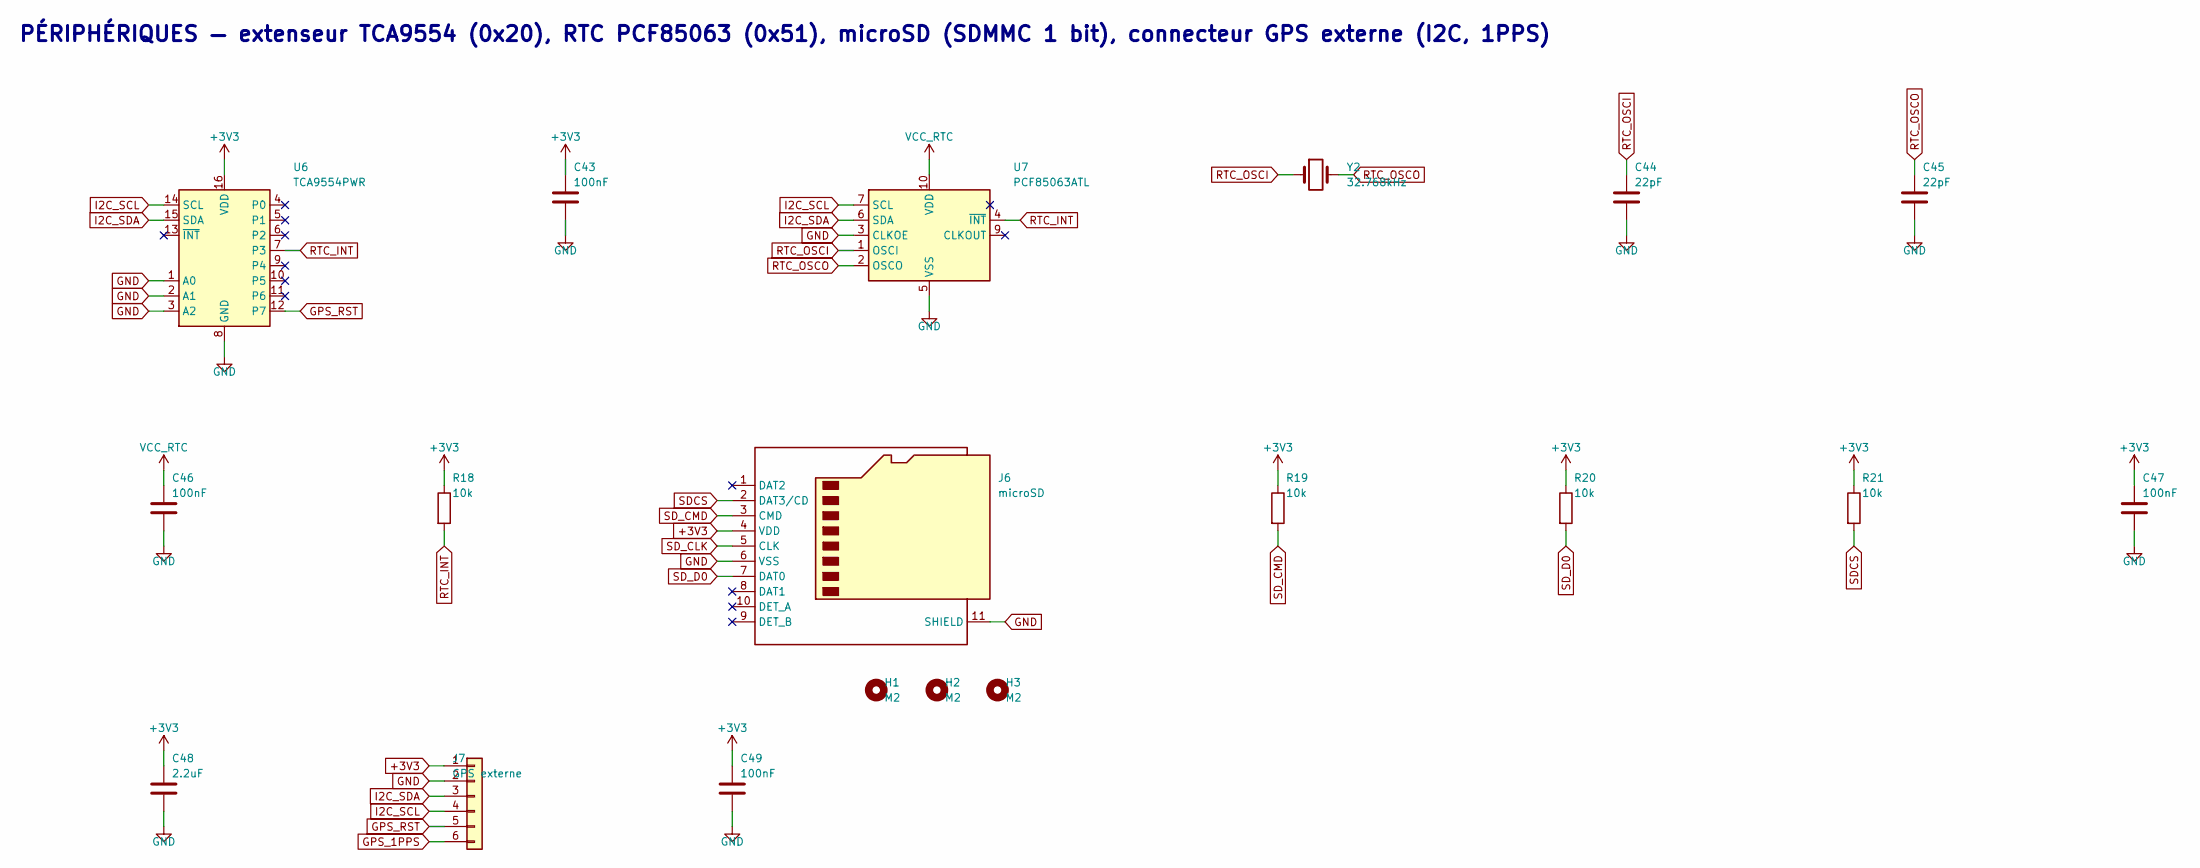
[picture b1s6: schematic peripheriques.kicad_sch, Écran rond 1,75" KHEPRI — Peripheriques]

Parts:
C43, C46, C47, C49: 100nF; C_0402_1005Metric
C44, C45: 22pF; C_0402_1005Metric
C48: 2.2uF; C_0603_1608Metric
H1, H2, H3: M2; MountingHole_2.2mm_M2
J6: microSD; microSD_HC_Hirose_DM3AT-SF-PEJM5
J7: GPS externe; JST_SH_SM06B-SRSS-TB_1x06-1MP_P1.00mm_Horizontal
R18, R19, R20, R21: 10k; R_0402_1005Metric
U6: TCA9554PWR; TSSOP-16_4.4x5mm_P0.65mm
U7: PCF85063ATL; DFN-10-1EP_2.6x2.6mm_P0.5mm_EP1.3x2.2mm
Y2: 32.768kHz; Crystal_SMD_3215-2Pin_3.2x1.5mm

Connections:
+3V3: C43.1, C47.1, C48.1, C49.1, J6.4 (VDD), J7.1, R18.1, R19.1, R20.1, R21.1, U6.16 (VDD); also elsewhere on the board
GND: C43.2, C44.2, C45.2, C46.2, C47.2, C48.2, C49.2, J6.6 (VSS), J6.11 (SHIELD), J7.2, U6.1 (A0), U6.2 (A1), U6.3 (A2), U6.8 (GND), U7.3 (CLKOE), U7.5 (VSS); also elsewhere on the board
GPS_1PPS: J7.6; also elsewhere on the board
GPS_RST: J7.5, U6.12 (P7)
I2C_SCL: J7.4, U6.14 (SCL), U7.7 (SCL); also elsewhere on the board
I2C_SDA: J7.3, U6.15 (SDA), U7.6 (SDA); also elsewhere on the board
RTC_INT: R18.2, U6.7 (P3), U7.4 (~INT)
RTC_OSCI: C44.1, U7.1 (OSCI), Y2.1
RTC_OSCO: C45.1, U7.2 (OSCO), Y2.2
SDCS: J6.2 (DAT3/CD), R21.2; also elsewhere on the board
SD_CLK: J6.5 (CLK); also elsewhere on the board
SD_CMD: J6.3 (CMD), R19.2; also elsewhere on the board
SD_D0: J6.7 (DAT0), R20.2; also elsewhere on the board
VCC_RTC: C46.1, U7.10 (VDD); also elsewhere on the board

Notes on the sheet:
PÉRIPHÉRIQUES — extenseur TCA9554 (0x20), RTC PCF85063 (0x51), microSD (SDMMC 1 bit), connecteur GPS externe (I2C, 1PPS)

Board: 4 copper layers, 87 parts (41 on the bottom side), 66 nets, no tracks yet.

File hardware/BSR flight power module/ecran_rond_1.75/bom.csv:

Référence;Valeur;Empreinte;Feuille;Description;DNP
J1;USB-C (flash / logs);Connector_USB:USB_C_Receptacle_HRO_TYPE-C-31-M-12;Alimentation;Prise USB-C 16P, USB 2.0;
R1;5.1k;Resistor_SMD:R_0402_1005Metric;Alimentation;Rd USB-C;
R2;5.1k;Resistor_SMD:R_0402_1005Metric;Alimentation;Rd USB-C;
D1;USBLC6-2SC6;Package_TO_SOT_SMD:SOT-23-6;Alimentation;Protection ESD USB;
D2;SMF5.0A;Diode_SMD:D_SOD-123F;Alimentation;TVS 5 V sur VBUS;
J2;IHM : 5V GND TX RX;Connector_JST:JST_PH_B4B-PH-K_1x04_P2.00mm_Vertical;Alimentation;JST PH 2,0 mm vers la carte façade : 1 = +5 V, 2 = GND, 3 = TX (GPIO17, sortie ESP32), 4 = RX (GPIO18);
D3;B5819W;Diode_SMD:D_SOD-123;Alimentation;OU diode : USB (Schottky 1 A 40 V);
D4;B5819W;Diode_SMD:D_SOD-123;Alimentation;OU diode : connecteur (Schottky 1 A 40 V);
C1;10uF;Capacitor_SMD:C_0805_2012Metric;Alimentation;;
C2;100nF;Capacitor_SMD:C_0402_1005Metric;Alimentation;;
U2;AP63203WU;Package_TO_SOT_SMD:TSOT-23-6;Alimentation;Buck 5 V -> 3,3 V 2 A, 1,1 MHz, sortie fixe (FB relié à la sortie);
R3;100k;Resistor_SMD:R_0402_1005Metric;Alimentation;Enable buck;
C3;100nF;Capacitor_SMD:C_0402_1005Metric;Alimentation;Bootstrap;
L1;4.7uH;Inductor_SMD:L_Taiyo-Yuden_NR-40xx;Alimentation;Self buck 4,7 µH ≥ 2,5 A sat.;
C4;22uF;Capacitor_SMD:C_0805_2012Metric;Alimentation;;
C5;22uF;Capacitor_SMD:C_0805_2012Metric;Alimentation;;
C6;100nF;Capacitor_SMD:C_0402_1005Metric;Alimentation;;
FB1;600R@100MHz;Inductor_SMD:L_0603_1608Metric;Alimentation;Filtrage 3,3 V analogique codec;
C7;10uF;Capacitor_SMD:C_0805_2012Metric;Alimentation;;
C8;100nF;Capacitor_SMD:C_0402_1005Metric;Alimentation;;
NT1;AGND=GND;NetTie:NetTie-2_SMD_Pad0.5mm;Alimentation;Point de masse unique audio;
BT1;CR1220;Battery:BatteryHolder_LINX_BAT-HLD-012-SMT;Alimentation;"Pile de sauvegarde RTC + démarrage à chaud GPS ; support CMS Linx BAT-HLD-012-SMT, côté écran";
D5;BAT54C;Package_TO_SOT_SMD:SOT-23;Alimentation;OU diode 3,3 V / pile -> VCC_RTC;
C9;100nF;Capacitor_SMD:C_0402_1005Metric;Alimentation;;
U1;ESP32-S3-WROOM-1-N16R8;RF_Module:ESP32-S3-WROOM-1;MCU;Module ESP32-S3-WROOM-1-N16R8 : ESP32-S3R8 + flash 16 Mo, antenne PCB, certifié CE/FCC. IO35-37 utilisés par la PSRAM octale (laisser en l air), IO47/48 libres. Antenne au bord de carte, zone sans cuivre dessous sur toutes les couches.;
C13;100nF;Capacitor_SMD:C_0402_1005Metric;MCU;Découplage module, au plus près de la broche 2;
C18;1uF;Capacitor_SMD:C_0402_1005Metric;MCU;Découplage module;
C19;22uF;Capacitor_SMD:C_0805_2012Metric;MCU;Réservoir module (pics d émission Wi-Fi);
R5;10k;Resistor_SMD:R_0402_1005Metric;MCU;Pull-up EN;
C20;1uF;Capacitor_SMD:C_0402_1005Metric;MCU;Délai reset (RC recommandé par Espressif);
SW1;RESET;Button_Switch_SMD:SW_SPST_PTS810;MCU;Bouton reset;
R6;10k;Resistor_SMD:R_0402_1005Metric;MCU;Pull-up BOOT;
C21;100nF;Capacitor_SMD:C_0402_1005Metric;MCU;;
SW2;BOOT;Button_Switch_SMD:SW_SPST_PTS810;MCU;Bouton BOOT (GPIO0);
R7;22R;Resistor_SMD:R_0402_1005Metric;MCU;;
R8;22R;Resistor_SMD:R_0402_1005Metric;MCU;;
TP1;GPIO16;TestPoint:TestPoint_Pad_D1.0mm;MCU;Point de test GPIO16;
TP3;U0TXD;TestPoint:TestPoint_Pad_D1.0mm;MCU;Console UART0 TX;
TP4;U0RXD;TestPoint:TestPoint_Pad_D1.0mm;MCU;Console UART0 RX;
J3;"AMOLED 1.75"" CO5300 + CST9217";Connector_FFC-FPC:Hirose_FH26-31S-0.3SHW_2Rows-31Pins-1MP_P0.60mm_Horizontal;Ecran;Connecteur nappe écran, brochage relevé sur le schéma Waveshare (pins 2-3, 5-6, 8-9, 19, 24 non connectées);
C25;10uF;Capacitor_SMD:C_0805_2012Metric;Ecran;Alim écran;
C26;1uF;Capacitor_SMD:C_0402_1005Metric;Ecran;;
C27;100nF;Capacitor_SMD:C_0402_1005Metric;Ecran;;
R11;2.2k;Resistor_SMD:R_0402_1005Metric;Ecran;Pull-up I2C;
R12;2.2k;Resistor_SMD:R_0402_1005Metric;Ecran;Pull-up I2C;
U4;ES8311;Package_DFN_QFN:QFN-20-1EP_3x3mm_P0.4mm_EP1.65x1.65mm;Audio;"Codec audio ; CE à la masse -> adresse I2C 0x18";
R13;10k;Resistor_SMD:R_0402_1005Metric;Audio;CE bas : adresse 0x18;
C28;100nF;Capacitor_SMD:C_0402_1005Metric;Audio;PVDD/DVDD;
C29;1uF;Capacitor_SMD:C_0402_1005Metric;Audio;AVDD;
C30;22pF;Capacitor_SMD:C_0402_1005Metric;Audio;;
C31;1uF;Capacitor_SMD:C_0402_1005Metric;Audio;;
C32;1uF;Capacitor_SMD:C_0402_1005Metric;Audio;;
C33;1uF;Capacitor_SMD:C_0402_1005Metric;Audio;;
C34;22pF;Capacitor_SMD:C_0402_1005Metric;Audio;CEM;
C35;22pF;Capacitor_SMD:C_0402_1005Metric;Audio;CEM;
C36;22pF;Capacitor_SMD:C_0402_1005Metric;Audio;CEM;
C37;1uF;Capacitor_SMD:C_0603_1608Metric;Audio;Couplage;
C38;1uF;Capacitor_SMD:C_0603_1608Metric;Audio;Couplage;
R14;150k;Resistor_SMD:R_0402_1005Metric;Audio;Gain ampli;
R15;150k;Resistor_SMD:R_0402_1005Metric;Audio;Gain ampli;
U5;NS4150B;Package_SO:SOIC-8_3.9x4.9mm_P1.27mm;Audio;Ampli classe D 3 W mono;
R16;0R;Resistor_SMD:R_0402_1005Metric;Audio;Commande ampli (GPIO46);
R17;10k;Resistor_SMD:R_0402_1005Metric;Audio;Pull-down : ampli coupé par défaut;
C39;1uF;Capacitor_SMD:C_0402_1005Metric;Audio;;
C40;10uF;Capacitor_SMD:C_0805_2012Metric;Audio;Alim ampli;
C41;100nF;Capacitor_SMD:C_0402_1005Metric;Audio;;
C42;1uF;Capacitor_SMD:C_0402_1005Metric;Audio;;
J5;HP 8R 2W;Connector_Molex:Molex_PicoBlade_53398-0271_1x02-1MP_P1.25mm_Vertical;Audio;Haut-parleur, MX1.25 2P;
U6;TCA9554PWR;Package_SO:TSSOP-16_4.4x5mm_P0.65mm;Peripheriques;"Extenseur E/S : P3 = RTC_INT, P7 = reset GPS ; P0-P2, P4-P6 non utilisés";
C43;100nF;Capacitor_SMD:C_0402_1005Metric;Peripheriques;;
U7;PCF85063ATL;Package_DFN_QFN:DFN-10-1EP_2.6x2.6mm_P0.5mm_EP1.3x2.2mm;Peripheriques;RTC I2C, alimentée par VCC_RTC (3,3 V ou pile);
Y2;32.768kHz;Crystal:Crystal_SMD_3215-2Pin_3.2x1.5mm;Peripheriques;Quartz horloger 12,5 pF;
C44;22pF;Capacitor_SMD:C_0402_1005Metric;Peripheriques;;
C45;22pF;Capacitor_SMD:C_0402_1005Metric;Peripheriques;;
C46;100nF;Capacitor_SMD:C_0402_1005Metric;Peripheriques;;
R18;10k;Resistor_SMD:R_0402_1005Metric;Peripheriques;Pull-up INT RTC (drain ouvert);
J6;microSD;Connector_Card:microSD_HC_Hirose_DM3AT-SF-PEJM5;Peripheriques;Lecteur microSD, SDMMC 1 bit (CMD GPIO1, CLK GPIO2, D0 GPIO3, D3 GPIO41);
R19;10k;Resistor_SMD:R_0402_1005Metric;Peripheriques;;
R20;10k;Resistor_SMD:R_0402_1005Metric;Peripheriques;;
R21;10k;Resistor_SMD:R_0402_1005Metric;Peripheriques;;
C47;100nF;Capacitor_SMD:C_0402_1005Metric;Peripheriques;;
C48;2.2uF;Capacitor_SMD:C_0603_1608Metric;Peripheriques;;
J7;GPS externe;Connector_JST:JST_SH_SM06B-SRSS-TB_1x06-1MP_P1.00mm_Horizontal;Peripheriques;"JST-SH 1,0 mm 6P vers module GPS externe (ex. LC76G + antenne) : 1 = 3V3, 2 = GND, 3 = SDA, 4 = SCL, 5 = RESET (TCA9554 P7), 6 = 1PPS (GPIO21) ; même bus I2C que l ancien LC76G intégré";
C49;100nF;Capacitor_SMD:C_0402_1005Metric;Peripheriques;Découplage alim GPS externe;
H1;M2;MountingHole:MountingHole_2.2mm_M2;Peripheriques;Trou de fixation M2;
H2;M2;MountingHole:MountingHole_2.2mm_M2;Peripheriques;Trou de fixation M2;
H3;M2;MountingHole:MountingHole_2.2mm_M2;Peripheriques;Trou de fixation M2;
